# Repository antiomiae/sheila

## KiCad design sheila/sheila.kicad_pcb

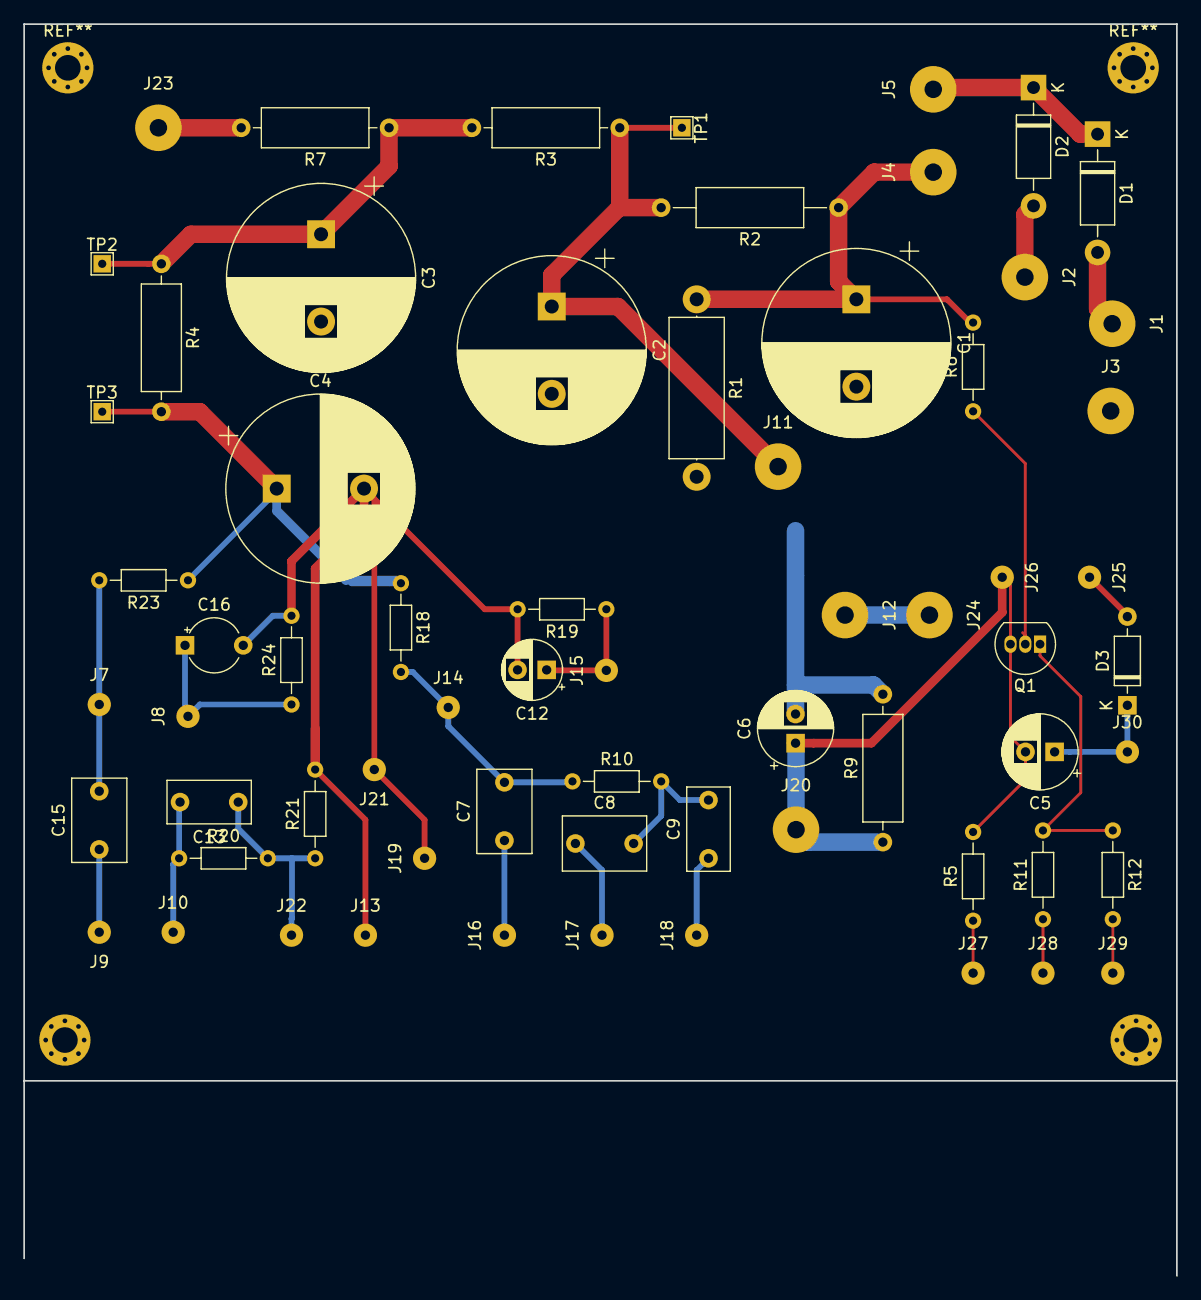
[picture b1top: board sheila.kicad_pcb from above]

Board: 2 copper layers, 99.0 x 107.5 mm, 66 parts (0 on the bottom side), 29 nets.

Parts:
C1, C2, C3, C4: 47uF/350V; CP_Radial_D16.0mm_P7.50mm
C5: 220uF/16V; CP_Radial_D6.3mm_P2.50mm
C6: 100uF/25V; CP_Radial_D6.3mm_P2.50mm
C7: 470pF; C_Rect_L7.0mm_W4.5mm_P5.00mm
C8, C15: 0.022uF; C_Rect_L7.0mm_W4.5mm_P5.00mm
C9: 0.01uF; C_Rect_L7.0mm_W3.5mm_P5.00mm
C12: 1uF/25V; CP_Radial_D5.0mm_P2.50mm
C13: 0.001uF; C_Rect_L7.0mm_W3.5mm_P5.00mm
C16: 0.68uF/25V; CP_Radial_Tantal_D4.5mm_P5.00mm
D1, D2: UF4007; D_DO-41_SOD81_P10.16mm_Horizontal
D3: D_ALT; D_DO-35_SOD27_P7.62mm_Horizontal
J1: PT_A; SolderWirePad_1x01_Drill1.5mm
J2: PT_B; SolderWirePad_1x01_Drill1.5mm
J3: PT_CT; SolderWirePad_1x01_Drill1.5mm
J4: S2_A; SolderWirePad_1x01_Drill1.5mm
J5: S2_B; SolderWirePad_1x01_Drill1.5mm
J7: U1B_6_A; SolderWirePad_1x01_Drill0.8mm
J8: U1B_8_K; SolderWirePad_1x01_Drill0.8mm
J9: GAIN1_SEND; SolderWirePad_1x01_Drill0.8mm
J10: GAIN1_RETURN; SolderWirePad_1x01_Drill0.8mm
J11: OT1_A; SolderWirePad_1x01_Drill1.5mm
J12: OT1_B; SolderWirePad_1x01_Drill1.5mm
J13: SHIELD; SolderWirePad_1x01_Drill0.8mm
J14: U1A_A_1; SolderWirePad_1x01_Drill0.8mm
J15: U1A_K_3; SolderWirePad_1x01_Drill0.8mm
J16: TS_T; SolderWirePad_1x01_Drill0.8mm
J17: TS_B; SolderWirePad_1x01_Drill0.8mm
J18: TS_M; SolderWirePad_1x01_Drill0.8mm
J19: TS_GND; SolderWirePad_1x01_Drill0.8mm
J20: U2_K_3; SolderWirePad_1x01_Drill1.5mm
J21: GAIN1_GND; SolderWirePad_1x01_Drill0.8mm
J22: U1A_G_2; SolderWirePad_1x01_Drill0.8mm
J23: U2_S_9; SolderWirePad_1x01_Drill1.5mm
J24: U2_A_7; SolderWirePad_1x01_Drill1.5mm
J25: PT_H1; SolderWirePad_1x01_Drill0.8mm
J26: PT_H2; SolderWirePad_1x01_Drill0.8mm
J27: LED1_R; SolderWirePad_1x01_Drill0.8mm
J28: LED1_G; SolderWirePad_1x01_Drill0.8mm
J29: LED1_B; SolderWirePad_1x01_Drill0.8mm
J30: LED1_A; SolderWirePad_1x01_Drill0.8mm
Q1: BC549; TO-92_Inline
R1: 220k/1W; R_Axial_DIN0414_L11.9mm_D4.5mm_P15.24mm_Horizontal
R2: 100R/1W; R_Axial_DIN0309_L9.0mm_D3.2mm_P15.24mm_Horizontal
R3, R7: 1K/1W; R_Axial_DIN0309_L9.0mm_D3.2mm_P12.70mm_Horizontal
R4: 10K/1W; R_Axial_DIN0309_L9.0mm_D3.2mm_P12.70mm_Horizontal
R5, R11, R12, R19: 1.2K; R_Axial_DIN0204_L3.6mm_D1.6mm_P7.62mm_Horizontal
R6: 1M; R_Axial_DIN0204_L3.6mm_D1.6mm_P7.62mm_Horizontal
R9: 130R/1W; R_Axial_DIN0309_L9.0mm_D3.2mm_P12.70mm_Horizontal
R10: 56K; R_Axial_DIN0204_L3.6mm_D1.6mm_P7.62mm_Horizontal
R18, R23: 100K; R_Axial_DIN0204_L3.6mm_D1.6mm_P7.62mm_Horizontal
R20, R21: 220K; R_Axial_DIN0204_L3.6mm_D1.6mm_P7.62mm_Horizontal
R24: 2.7K; R_Axial_DIN0204_L3.6mm_D1.6mm_P7.62mm_Horizontal
TP1, TP2, TP3: TestPoint; TestPoint_THTPad_1.5x1.5mm_Drill0.7mm

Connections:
/A: C5.2, C6.1, J20.1, J26.1, Q1.3, R5.2, R9.1
/B+: C1.1, J4.1, R1.1, R2.1, R6.2
/B+1: C2.1, J11.1, R2.2, R3.1, TP1.1
/B+2: C3.1, R3.2, R4.1, R7.1, TP2.1
/B+3: C4.1, R4.2, R18.1, R23.1, TP3.1
/P_A: D1.2, J1.1
/P_B: D2.2, J2.1
GND: C1.2, C2.2, C3.2, C4.2, C6.2, C12.2, C16.2, J3.1, J13.1, J19.1, J21.1, R1.2, R9.2, R19.2, R21.2, R24.2
unnamed: C5.1, D3.1, J30.1
unnamed: C7.1, J16.1
unnamed: C7.2, J14.1, R10.1, R18.2
unnamed: C8.1, J17.1
unnamed: C8.2, C9.2, R10.2
unnamed: C9.1, J18.1
unnamed: C12.1, J15.1, R19.1
unnamed: C13.1, J22.1, R20.2, R21.1
unnamed: C13.2, J10.1, R20.1
unnamed: C15.1, J9.1
unnamed: C15.2, J7.1, R23.2
unnamed: C16.1, J8.1, R24.1
unnamed: D1.1, D2.1, J5.1
unnamed: D3.2, J25.1
unnamed: J27.1, R5.1
unnamed: J28.1, R11.1
unnamed: J29.1, R12.2
unnamed: J12.1, J24.1
unnamed: J23.1, R7.2
unnamed: Q1.1, R11.2, R12.1
unnamed: Q1.2, R6.1

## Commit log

2019-02-04 Remove backup file from git
2019-02-04 Use project directory in library paths
2019-02-04 Update component values
2019-02-04 Ignore bak files
